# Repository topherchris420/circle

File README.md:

# CIRCLE

<div align="center">

### Close the loop. Keep the evidence.

**An open research test bench for physiological sensing, adaptive feedback, and human authority.**

[Run a session](#quick-start) · [Follow the evidence](#how-circle-works) · [Test the limits](#test-the-failure-modes) · [Human authority](#human-authority-in-the-loop) · [Explore the project](#what-you-can-examine) · [Contribute](#contributing)

<br />

<sub>One simulated session. Several physiological pathways. Every decision on the same timeline.<br />Ground truth is available to the evaluator; the controller works from device records alone.</sub>

</div>

---

**When a system senses a change and responds, what would let another researcher trust the record?**

CIRCLE makes that question runnable. It reconstructs physiological signals from simulated sensor codes, decides when haptic guidance is warranted, and preserves the evidence from the original samples through the observed cue. An independent auditor then rebuilds the session from its raw bundle.

The research ambition is a closed-loop human-state platform whose actions remain inspectable, reproducible, and subject to meaningful consent. Today, you can run the digital test bench, challenge its controller, audit its decisions, and examine a standalone cryptographic consent gate. The hardware is a design awaiting physical validation.

> [!WARNING]
> **ENGINEERING REVIEW ONLY.** Experimental research hardware and software. This repository is not approved for fabrication or human connection and does not establish medical-device, electrical-safety, EMC, or measurement-performance claims. All physiological results shown here come from simulation.

## Quick start

### Open the local workbench

The easiest way to explore CIRCLE is its local browser workbench. Choose one of
eight guided scenarios, run an active or sham session, and see the measurement
checks alongside an independent audit. Your session history, interactive reports,
and downloadable evidence stay on your computer.

```bash
git clone https://github.com/topherchris420/circle.git
cd circle
python -m pip install -r requirements.txt
python tools/run_workbench.py
```

Requires **Python 3.11+**. The browser opens at **http://127.0.0.1:8765**. Keep the
terminal running; you can close and reopen the browser tab without losing the
session. Start with **A clear signal**, then try **A loose sensor** to explore why
measurement quality and evidence integrity are separate results. No account,
device, or API key is needed. All feedback is simulated.

[Workbench guide, downloads, and troubleshooting](docs/workbench.md) ·
Use `--port 8766` if the default port is busy, or `--no-browser` to open it manually.

### Run your first session

Prefer the command line? You need **Python 3.11+**, Git, and the dependencies in [`requirements.txt`](requirements.txt). No device, account, API key, or model server is required for the simulation.

```bash
git clone https://github.com/topherchris420/circle.git
cd circle
python -m pip install -r requirements.txt
python tools/run_physiology_twin.py --output outputs/physiology --audit
```

<details>
<summary>Prefer an isolated Python environment?</summary>

After cloning and entering `circle`, create a virtual environment with `python -m venv .venv`. Activate it with `source .venv/bin/activate` on macOS/Linux or `.\.venv\Scripts\Activate.ps1` in Windows PowerShell, then run the install and experiment commands above. If your system names Python `python3`, use that command instead.

</details>

The default run simulates **six minutes**: rest, breath hold, a stressor, and recovery with adaptive haptic guidance. It also runs a matched sham arm for comparison, exports the session, scores estimates against hidden truth, and audits the exported evidence.

### Open the report and follow one decision

Open **`outputs/physiology/report.html`** in your browser. The report is self-contained: zoom the traces, open a row in the decision ledger, and follow its evidence down to the source samples.

| Question | Where to look |
| --- | --- |
| What did the controller know at that moment? | Input cutoff, availability times, features, and exact sample ranges |
| Why did it act—or hold? | Controller state, formula components, and quality-gate outcomes |
| Did the cue occur? | Command, electrical onset, and IMU-observed vibration |
| What changes when cues are withheld? | Matched sham traces, under the twin's assumed response model |
| Can the record be reconstructed? | Decision replay and independent audit verdict |

A successful reconstruction reports **`REPLAY_MATCH`**. That establishes agreement between the export and reconstruction from its inputs. The simulation scorecard separately measures agreement with the twin's truth.

To explore before running anything, open the [committed example report](diagrams/circle-physiology-session.html) locally after cloning. The image above is a static preview of that interface.

### Know what the run preserves

| Export | Purpose |
| --- | --- |
| `raw/*.csv.gz` | Sensor codes and timing records used for reconstruction |
| `session.ndjson` | Versioned device and derived records, lineage, gaps, and intervention chains |
| `closed_loop_ledger.json` | Every controller evaluation and the evidence it read |
| `analysis.json` · `scorecard.json` | Recovered estimates and checks against simulated truth |
| `truth.json` · `counterfactual.json` | Evaluator truth and the matched opposite arm; never controller inputs |
| `manifest.json` · `passport.txt` | Configuration, software provenance, artifact hashes, and session summary |
| `report.html` | Interactive view of the traces, decisions, scorecard, and execution evidence |

The [pipeline methods](docs/physiology-pipeline.md) explain how each channel and metric is derived.

## How CIRCLE works

The central question is **what gives this system grounds to act?**

A rise in heart rate is one observation. A rise in skin conductance is another. CIRCLE requires agreement across the cardiovascular and electrodermal pathways, sufficient signal quality, and a sustained observed state before guidance can begin.

| Stage | Evidence CIRCLE preserves |
| --- | --- |
| **Observe** | Raw skin conductance (EDA), optical pulse (PPG), motion (IMU), and synchronization records; device times, sequence numbers, availability, and declared gaps |
| **Infer** | Recovered physiological features, with lineage to the exact samples used |
| **Decide** | State, input cutoff, formula components, and explicit outcomes for acting, holding, or stopping |
| **Intervene** | The scheduled command, electrical onset, and vibration detected from IMU samples |
| **Reconstruct** | Analysis and derived records rebuilt from raw inputs, followed by an explicit replay verdict |

Three rules make the loop inspectable:

- **A decision can use only evidence available at the time.** A sample must have been available by the decision time and been taken at or before the input cutoff. FIFO stalls, delayed delivery, and missing samples remain visible in the record.
- **Holding is a decision.** Motion, poor contact, stale data, or disagreeing pathways can prevent guidance. After impairment, the controller requires a full clean **40-second evidence window** before treating an elevated state as sustained; repeated quality loss during guidance stops it.
- **Each stage earns its own evidence.** A command does not prove vibration, and vibration does not establish a physiological effect. `PHYSICALLY_OBSERVED` requires an observation record; in this test bench, that observation is simulated too.

The pipeline and controller consume the shared [`RawSession` boundary](models/physiology/loop.py) without importing hidden truth. The auditor reconstructs derived records instead of accepting their stored values. A derived record that disagrees with reconstruction remains detectable even if its checksums are rewritten; hashes alone do not authenticate the underlying data.

Replay names its result: `REPLAY_MATCH`, `REPLAY_DIVERGENCE`, `TIMING_VIOLATION`, `VERSION_MISMATCH`, `EVIDENCE_INTEGRITY_FAILURE`, `MISSING_SOURCE`, or `INSUFFICIENT_EVIDENCE`.

Read the [evidence contract and failure history](docs/closed-loop-evidence.md), [record schema](contracts/session-record.schema.json), and [auditor](models/physiology/audit.py).

## Test the failure modes

Change the conditions, then inspect whether the controller's behavior is justified:

```bash
# Same seed, sham arm: decisions recorded, cues withheld
python tools/run_physiology_twin.py --sham --no-counterfactual --output outputs/sham --audit

# Eight scenario families, including motion, contact loss, and timing faults
python tools/run_physiology_twin.py --scenarios --output outputs/scenarios

# Audit an existing export without rerunning the twin
python tools/audit_physiology_run.py outputs/physiology
```

The scenario suite tests both sides of the decision: refusing unwarranted guidance **and** acting when a warranted state becomes observable. A controller that always holds cannot pass. The [scenario definitions](models/physiology/scenarios.py) specify each disturbance and judge the result against hidden truth.

To inspect a deliberate loss of measurement quality, export the poor-contact scenario:

```bash
python tools/run_physiology_twin.py --scenario poor_contact --output outputs/poor-contact --audit
```

With the default seed 7, this run withholds guidance, passes **14 of 19 scorecard checks**, and returns exit code **1** because five checks fail. Its audit still reports **`REPLAY_MATCH`**: the impaired session can be reconstructed faithfully. Measurement quality and evidence integrity answer different questions. Open `outputs/poor-contact/report.html` to examine both.

The twin assumes that paced breathing changes its simulated physiology. Active-versus-sham comparisons test the software under that assumption; a physiological effect in people would need separate evidence.

## Results you can inspect

The checked-in physiology benchmark covers **50 seeds, 100–149**. Its numbers describe agreement with **simulated truth**, under the stated scoring conditions.

| Measurement | Recorded result | Evaluation condition |
| --- | --- | --- |
| Heartbeat detection | Mean F1 **0.9999** | Motion-free PPG; ±50 ms matching tolerance |
| Heart rate | Mean absolute error **0.39 bpm** | Recovered from raw sensor codes |
| HRV: RMSSD | Mean absolute error **1.5 ms** | 60-second windows |
| Respiratory rate | Mean absolute error **0.36 breaths/min** | Recovered respiratory modulation |
| Skin conductance response detection | Mean sensitivity **0.98**, positive predictive value **1.00** | Motion-free responses ≥0.05 µS |
| PPG FIFO timing | Worst error **39.18 µs** | Reconstructed sample timestamps |
| Haptic onset detection | Worst error **2.97 ms** | IMU detection versus the twin's onset |

**999 of 1,000 checks passed.** Seed 147 failed the skin-conductance response sensitivity threshold: **11 of 14 responses detected**, below the required 0.85 sensitivity. The [benchmark](docs/physiology-benchmark.json) retains the failure; the [methods](docs/physiology-pipeline.md) explain the overlapping responses and resolution limits.

**Controller 1.2.0 passed 240 of 240 runs** across eight scenario families on fresh confirmatory seeds **600–629**. The [scenario benchmark](docs/scenario-benchmark.json) records the conditions. An earlier controller passed 199 of 210 runs; its failures exposed guidance starting from an elevated state that had already resolved during a motion-obscured interval. That finding produced the clean-window precondition and evaluation on new seeds. The [evidence history](docs/closed-loop-evidence.md) preserves both rounds.

These results establish software behavior under the twin's models. Sensor accuracy, assembled-hardware performance, and human outcomes each need their own measurements.

## Human authority in the loop

CIRCLE's consent work asks a second question: **who has authority to turn a proposal into a change?** Two mechanisms address different parts of that boundary.

### Consent-by-Design

[`circle_authority.py`](circle_authority.py) implements a standalone deterministic consent gate. A restricted proposal becomes an immutable envelope containing its mutation, proposal timestamp, state-history hash, action UUID, and an initially empty signature slot. It waits as data while the loop continues processing telemetry.

| Action state | What happens |
| --- | --- |
| `PENDING_SIGNATURE` | The proposal is registered; telemetry continues; the mutation waits. |
| `EXECUTED` | Matching consent verifies against the registered Ed25519 human public key and the mutation completes; signature and execution frame are recorded. |
| `REJECTED` | Proposal, consent, or execution checks fail; no automatic retry follows. |

```bash
python tools/run_authority_demo.py
```

The demo receives a proposal at frame 1, continues telemetry through frames 2 and 3, and executes the signed mutation at frame 4. Repeated runs produce identical replay records using fixed **test-only** credentials.

**The gate is standalone; the physiological controller and protocol runner do not yet route through it.** Its signature authenticates the UUID. Durable bindings between UUIDs and envelopes, protected replay storage, and execution-time state checks are host responsibilities. The [consent integration contract](docs/consent-by-design.md) specifies these boundaries and failure behavior.

### Authorize a bounded experiment

The [protocol runner](models/protocols.py) validates proposed experiments against deterministic rules: simulation-only targets, mandatory sham arms, preserved timing margins, held-out seed checks, and corrected statistical comparisons. A named reviewer record binds authorization to the protocol's SHA-256. This record is separate from the Ed25519 consent mechanism.

<details>
<summary>Validate, authorize, and run the example protocol</summary>

```bash
python tools/run_protocol.py validate experiments/protocols/paced-breathing-arousal.json
python tools/run_protocol.py authorize experiments/protocols/paced-breathing-arousal.json --reviewer "Your Name" --output outputs/auth.json
python tools/run_protocol.py run experiments/protocols/paced-breathing-arousal.json --authorization outputs/auth.json --output outputs/protocol-result.json
```

Run the quick start first so `outputs/` exists. Review the protocol before recording authorization in your name. See the [protocol evidence contract](docs/closed-loop-evidence.md#ai-may-propose-circle-executes-the-contract) for validation and interpretation boundaries.

</details>

AI can help formulate and examine a proposal. The deterministic checks and human authorization define what may proceed.

## What you can examine

The [capability registry](capabilities.json) records implemented code, evidence, and limits. Use it to distinguish a runnable module from a design or research hypothesis.

| Area | Available now | Current boundary |
| --- | --- | --- |
| [Local workbench](docs/workbench.md) | Guided scenarios, active/sham controls, progress, cancellation, history, report viewing, and evidence downloads | Local simulation interface; no live hardware or hosted accounts |
| [Physiology pipeline](docs/physiology-pipeline.md) | Sensor reconstruction, controller, interactive report, export, and audit | Exercised against the twin |
| [Consent gate](docs/consent-by-design.md) | Ed25519 verification, immutable action envelopes, and hash-linked replay | Standalone simulation; integration remains open |
| [Acquisition](docs/hardware-sources.md) | Ingestion, clock mapping, declared gaps, simulated link faults, and recorded replay | No live biosignal device connected here |
| [OpenBCI Cyton](docs/openbci-cyton.md) | 8/16-channel ADS1299 bridge, register read-back, and an internal-signal electronic phantom | Exercised against a simulated board |
| [Oura ring](docs/hardware-sources.md#oura-ring-over-bluetooth-le-experimental-live-bridge) | Experimental BLE acquisition bridge | Exercised against a fake ring |
| [Muse Gadget](docs/hardware-sources.md) | Capability discovery, recorded refusals, protocol validation, optional operator notifications | Supplies no physiological streams; no paired-gadget validation |
| [Rev B hardware](docs/architecture.md) | Schematics, board outlines, design manifest, and engineering review gates | Designed, not built; main and optical boards unrouted |
| [Firmware](docs/timing-and-data-model.md) | Timing behavior modeled by the twin; pin map and initialization specification | Implementation remains open |

### Exercise the acquisition boundary

```bash
python tools/run_acquisition_demo.py
python tools/openbci_cyton.py self-test
python tools/muse_gadget.py capabilities --simulate
```

These examples need no hardware. **The Cyton phantom is a practical route toward physical evidence:** its ADS1299 internal test signal can supply known input through the acquisition chain without a person. The [Cyton guide](docs/openbci-cyton.md) explains the simulated scorecard and optional real-board procedure.

Every source faces the same stream contract. The Cyton provides biopotentials rather than the EDA, PPG, and other streams the physiology controller requires, so the closed loop refuses it and records why. Accepted closed-loop actuator targets are currently **`SIMULATED`** and **`NONE`**.

### From simulation to an instrument

Rev B is designed to make acquisition timing and intervention evidence observable. The **85 × 55 mm main board** combines an ESP32-S3, ADS1220 EDA front end, ICM-42688-P IMU, SDMMC storage, and DRV2605L haptics with current-edge detection. A **25 × 18 mm optical board** carries a MAX30102 red/IR sensor. Isolation, interlocks, and current limiting are design provisions awaiting independent review and measurement.

<div align="center">

<sub>Intended geometry only. Designed, not built.</sub>

</div>

[Main schematic](hardware/reports/pdf/circle-main.pdf) · [Optical schematic](hardware/reports/pdf/circle-ppg.pdf) · [Safety analysis](docs/safety-analysis.md) · [Bring-up plan](docs/board-bringup-and-validation-plan.md) · [3D viewer](diagrams/circle-3d-viewer.html)

The [checked-in verification summary](hardware/reports/verification-summary.json) records passing software scopes and **incomplete full verification** because fresh hardware checks were not run. Archived KiCad 10.0.5 schematic reports pass; PCB reports retain an open allowlist of **52 unrouted nets**. The [18 open review gates](hardware/review-gates.json) do not authorize fabrication or human use.

The next physical milestones are known-input phantoms, bench fixtures, isolation testing, and actuator loopback. The [physical evidence ladder](docs/physical-evidence-ladder.md) defines what each stage must establish before later work can proceed.

### Research extensions

The core instrument can stand independently of the research questions attached to it. The [module registry check](tools/check_module_registry.py) enforces that boundary.

| Extension | Research question or method | Evidence boundary |
| --- | --- | --- |
| [Resonance](docs/resonance-architecture.md) | Coupled-cavity models, blinded comparisons, and [falsifiable geometry hypotheses](docs/resonance-hypotheses.md) | Experimental simulation; no chamber or measured geometry effect |
| [Emergence](docs/emergence-architecture.md) | ATOM correlation search against circular-shift surrogate nulls, with family-wise correction | Exploratory associations; no causal or consciousness claim |
| [PNT](docs/quantum-pnt-architecture.md) | Translation-only 15-state estimator versus an unaided baseline on shared simulated IMU data | Simulation benchmark; quantum sensing remains speculative |
| [R.A.I.N. protocol](docs/rain-circle-experiment-protocol.md) | Versioned experiment manifest, result, and analysis contracts | Contracts here; executor elsewhere |
| [Mathematics intake](docs/MATH_RESEARCH.md) | Proposed packet-loss and clock-drift comparison with a negative control | Research design; implementation and testing remain open |

Each hypothesis needs a predefined comparison, appropriate controls, and a result that could count against it.

## Verify your scope

```bash
# Software, simulation, and deterministic artifact checks
python tools/verify_release.py --software-only

# Full package verification, requiring the pinned KiCad 10.0.5 toolchain
python tools/verify_release.py

# Inspect current review gates and derived authorization boundaries
python tools/check_review_gates.py
```

For the unit and property suite alone, run `python -m unittest discover -s tests`.

Software-only verification reports `SOFTWARE_VERIFIED` when its checks pass. Full verification requires fresh KiCad checks and reports `INCOMPLETE` if the pinned toolchain is unavailable. Neither result closes physical validation or human-use gates. See [verification scopes](docs/verification-scopes.md) and [`toolchain.json`](toolchain.json).

## Documentation

| If you want to… | Start here |
| --- | --- |
| Understand the measurement methods | [Physiology pipeline](docs/physiology-pipeline.md) |
| Examine timing, replay, and controller failures | [Closed-loop evidence](docs/closed-loop-evidence.md) |
| Integrate the consent reducer | [Consent-by-Design](docs/consent-by-design.md) |
| Add or evaluate an acquisition source | [Hardware sources](docs/hardware-sources.md) · [OpenBCI Cyton](docs/openbci-cyton.md) |
| Review the hardware design | [Architecture](docs/architecture.md) · [Safety analysis](docs/safety-analysis.md) |
| Plan physical validation | [Physical evidence ladder](docs/physical-evidence-ladder.md) · [Bring-up plan](docs/board-bringup-and-validation-plan.md) |
| Interpret verification status | [Verification scopes](docs/verification-scopes.md) · [Capability registry](capabilities.json) |

<details>
<summary>Repository map</summary>

| Path | Purpose |
| --- | --- |
| [`models/physiology/`](models/physiology) | Twin, sensors, pipeline, controller, report, evidence export, and audit |
| [`circle_authority.py`](circle_authority.py) | Consent state machine and replay payloads |
| [`models/acquisition/`](models/acquisition) | Ingestion, clock mapping, link faults, and recorded replay |
| [`models/openbci_cyton/`](models/openbci_cyton) | Cyton bridge, phantom analysis, and simulated board |
| [`models/protocols.py`](models/protocols.py) | Protocol validation, reviewer authorization, and simulation execution |
| [`models/session_records.py`](models/session_records.py) · [`contracts/`](contracts) | Record validation, provenance, lineage, and schemas |
| [`tools/`](tools) · [`tests/`](tests) | Experiments, auditors, verification tools, and regression checks |
| [`experiments/`](experiments) | Protocols and research configurations |
| [`hardware/`](hardware) | KiCad sources, interfaces, manifest, review gates, and reports |
| [`docs/`](docs) · [`diagrams/`](diagrams) | Methods, evidence boundaries, architecture, and visual explanations |

</details>

## Contributing

Useful contributions make a concrete question answerable:

- **Improve an estimator.** Compare it on fresh seeds and retain the cases where it fails.
- **Connect consent to an application path.** Define the restricted mutations, preserve durable UUID bindings, and demonstrate replay and crash-recovery behavior.
- **Strengthen acquisition.** Meet the stream and timing contracts, then exercise loss, delay, refusals, and replay. A Cyton owner can contribute an internal-signal phantom session without collecting personal biosignals.
- **Advance hardware or firmware.** Work through the review gates, timestamping requirements, and known-input validation plans.
- **Challenge a research hypothesis.** Define the comparison and a failure condition before running it; preserve the null result.

[Open an issue](https://github.com/topherchris420/circle/issues) with the question, proposed change, evidence it would produce, and a condition that would count as failure. Include the seed and replay verdict when reporting a simulation issue. [GitHub Actions](https://github.com/topherchris420/circle/actions) records current CI results.

## FAQ

<details>
<summary><strong>Can CIRCLE tell what someone is feeling?</strong></summary>

An arousal index is an engineering trigger. Physiological signals alone cannot establish a person's emotion, intent, diagnosis, or consciousness. The current twin is phenomenological and is not fitted to any person.

</details>

<details>
<summary><strong>Does consent gate every physiological cue?</strong></summary>

The Ed25519 authority module is implemented and tested independently. Wiring it into the physiological controller and protocol runner remains an open integration task.

</details>

<details>
<summary><strong>What does a passing audit establish?</strong></summary>

It establishes that the exported session satisfies the checked contracts and agrees with independent reconstruction from its raw inputs. It does not establish that those inputs accurately describe the physical world or that an intervention caused a change.

</details>

<details>
<summary><strong>Can I fabricate Rev B or connect it to a person?</strong></summary>

The boards are designed but unrouted. Fabrication and human connection remain unauthorized under the [open engineering review gates](hardware/review-gates.json). No physical sensor, bench, electrical-safety, EMC, or human-outcome validation has been performed here.

</details>

## License

[MIT](LICENSE). The license grants no approval to fabricate the hardware or connect it to a person; the engineering review boundaries above still apply.

## The premise

A human state is rarely one signal. The body offers many imperfect observations; understanding begins in the relationships among them.

CIRCLE's ambition is an instrument that can explain what it observed, account for what it changed, and preserve the person's authority over what happens next. Every experiment brings that ambition back to a record someone else can examine.

<div align="center">

**A Vers3Dynamics research project by Christopher Woodyard.**<br />
Built by one researcher. Held in common. Free to explore.

</div>

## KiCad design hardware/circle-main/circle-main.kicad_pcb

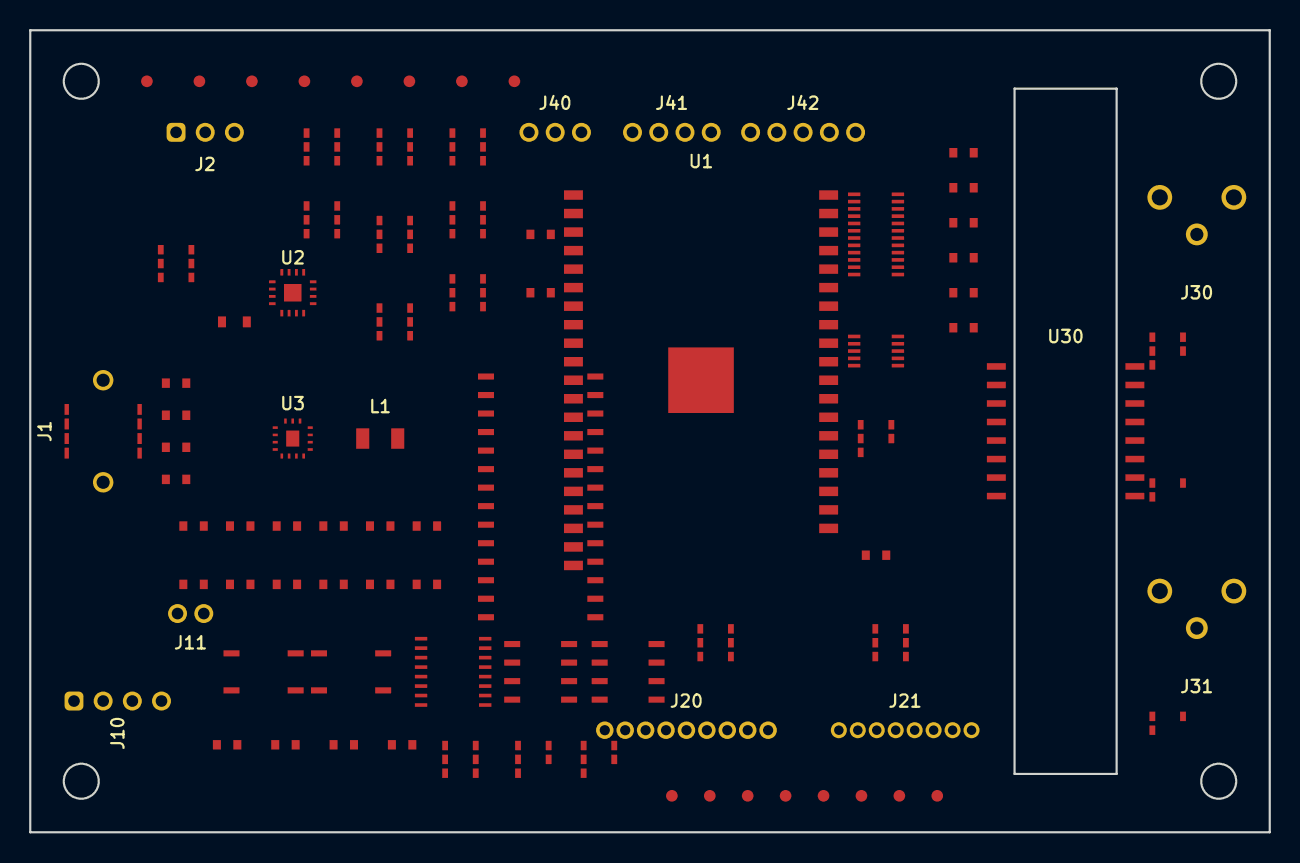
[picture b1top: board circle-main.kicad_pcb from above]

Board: 4 copper layers, 85.0 x 55.0 mm, 88 parts (0 on the bottom side), 42 nets, no tracks yet.

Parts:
D1: TPD4E05U06; SOT-23-6
D20, D21: ESD; SOT-23-6
D30: ESD_ISO; SOT-23-3
F1: USB_INPUT_FUSE; Fuse_0805
J1: USB4125-GF-A; USB_C_Receptacle
J2: LIPO_1S_NTC; JST_PH_S3B-PH-K
J10: EDA_ELECTRODES; JST_PH_S4B-PH-K
J11: CAL_INJ; Header_2P
J20: PPG_HEAD; JST_GH_9P
J21: MICROSD; Header_8P
J30: SYNC_IN_BNC; BNC_Horizontal
J31: SYNC_OUT_BNC; BNC_Horizontal
J40: HAPTIC; Header_3P
J41: INT_EXP; Header_4P
J42: EXT_EXP; Header_5P
JP1, JP2, JP3, JP4, JP5, JP6: JUMPER; R_0603
K1, K2: AQY212GS; SOIC-4
L1: 1.5uH; L_Bourns_SRN4018
Q1: SD_SW; SOT-23-6
Q2: PPG_LED_SW; SOT-23-6
Q3: HAPTIC_SW; SOT-23-6
Q4: ISO_SW; SOT-23-6
Q5: EXP_SW; SOT-23-6
Q7: EDA_SW; SOT-23-6
Q30: BSS138; SOT-23-3
R1, R2, R3, R4: 22R; R_0603
RSD1, RSD2, RSD3, RSD4, RSD5, RSD6: 33R; R_0603
RSH1, RSH2, RSH3, RSH4, RSH5, RSH6: 0.1R; R_0603
R_EDA_A1, R_EDA_A2: 49.9k; R_0603
R_EDA_B1, R_EDA_B2: 49.9k; R_0603
S1: BOOT; R_0603
S2: RESET; R_0603
S20: SAFE_EJECT; R_0603
TP1, TP2, TP3, TP4, TP5, TP6, TP7, TP8, TP9, TP10, TP11, TP12, TP13, TP14, TP15, TP16: TESTPOINT; TestPoint_Pad
U1: ESP32-S3-WROOM-1-N16R8; ESP32-S3-WROOM-1
U2: BQ24074RGTR; QFN-16-1EP
U3: TPS63070RNMR; WQFN-15-1EP
U4, U5, U13: TPS3700; SOT-23-6
U6: MCP23017; SOIC-28
U10: ADS1220; SOIC-16
U11: OPA2192; SOIC-8
U12: REF5020; SOIC-8
U14, U15: SN74LVC1G08; SOT-23-5
U20: ICM-42688-P; SOIC-24
U30: ISOW7742DWER; SOIC-16W
U31: TTL_COMP; SOT-23-5
U40: DRV2605L; SOIC-10
U41: TLV3201; SOT-23-5

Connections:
+3V3_DIG: J21.8, J41.4, JP1.2, JP2.2, JP3.2, JP4.2, JP5.2, JP6.2, L1.2, Q1.5, Q2.5, Q3.5, Q4.5, Q5.5, RSH1.2, RSH2.2, RSH3.2, RSH4.2, RSH5.2, RSH6.2, S1.2, S2.2, S20.2, TP2.1, TP4.1, TP6.1, TP8.1, TP10.1, TP12.1, TP14.1, TP16.1, U1.2, U3.5, U3.6, U3.7, U3.8, U3.9, U4.6, U5.6, U13.6, U14.5, U15.5, U30.1, U30.7, U41.3, U41.5
+3V3_EDA_A: Q7.5, U10.1, U10.16, U11.8, U12.1, U12.2, U12.7, U13.1
BAT_HUMAN_GND: D1.2, D1.5, D20.1, D20.2, D20.3, D20.4, D20.5, D20.6, D21.1, D21.2, D21.3, D21.4, D21.5, D21.6, J1.A1, J1.B1, J1.SH1, J1.SH2, J2.2, J2.3, J20.8, J20.9, J21.7, J40.3, J41.3, J42.5, K1.2, K2.2, Q1.2, Q1.4, Q1.6, Q2.2, Q2.4, Q2.6, Q3.2, Q3.4, Q3.6, Q4.2, Q4.4, Q4.6, Q5.2, Q5.4, Q5.6, Q7.2, Q7.4, Q7.6, S1.1, S2.1, S20.1, TP1.1, TP3.1, TP5.1, TP7.1, TP9.1, TP11.1, TP13.1, TP15.1, U1.1, U1.3, U1.22, U1.25, U1.26, U1.27, U1.39, U1.40, U1.41, U2.2, U2.3, U2.4, U2.5, U2.9, U2.10, U2.11, U2.12, U2.14, U2.15, U2.16, U2.17, U3.3, U3.4, U3.10, U3.13, U3.15, U3.16, U4.2, U4.4, U4.5, U5.2, U5.4, U5.5, U6.1, U6.2, U6.3, U6.4, U6.5, U6.6, U6.7, U6.8, U6.9, U6.10, U6.11, U6.12, U6.13, U6.14, U6.15, U6.16, U6.17, U6.18, U6.19, U6.20, U6.21, U6.22, U6.23, U6.24, U6.25, U6.26, U6.27, U6.28, U10.7, U10.8, U10.11, U10.12, U10.13, U10.14, U10.15, U11.4, U12.3, U12.4, U12.5, U12.6, U12.8, U13.2, U13.4, U13.5, U14.3, U15.3, U20.1, U20.2, U20.3, U20.4, U20.5, U20.6, U20.7, U20.8, U20.9, U20.10, U20.11, U20.12, U20.13, U20.14, U20.15, U20.16, U20.17, U20.18, U20.19, U20.20, U20.21, U20.22, U20.23, U20.24, U30.2, U30.6, U30.8, U40.1, U40.2, U40.3, U40.4, U40.5, U40.6, U40.7, U40.8, U40.9, U40.10, U41.2
EDA_ACTIVE: K1.1, K2.1, U15.4
EDA_ANALOG_GOOD: U13.3, U14.2
EDA_CS_N: U1.32, U10.3
EDA_DRDY: U1.37, U10.2
EDA_DRIVE_N: J10.2, J11.2, K2.3, K2.4, R_EDA_B1.1, R_EDA_B1.2, R_EDA_B2.1, R_EDA_B2.2, U11.5
EDA_DRIVE_P: J10.1, J11.1, K1.3, K1.4, R_EDA_A1.1, R_EDA_A1.2, R_EDA_A2.1, R_EDA_A2.2, U11.3
EDA_FW_REQUEST: U1.35, U14.1
EDA_MISO: U1.31, U10.6
EDA_MOSI: U1.30, U10.5
EDA_PREPARE: U14.4, U15.1
EDA_SCLK: U1.29, U10.4
EDA_SENSE_N: J10.4, U10.10, U11.6, U11.7
EDA_SENSE_P: J10.3, U10.9, U11.1, U11.2
HAPTIC_CURRENT_EDGE: J40.2, U1.36, U41.4
HAPTIC_VDRV: J40.1, U41.1
ISO_HEALTH_CHALLENGE: U1.28, U30.13
LAB_ISO_GND: D30.2, D30.3, J30.2, J30.3, J31.2, J31.3, Q30.2, U30.9, U30.14, U30.15, U31.2
PPG_INT: J20.5, U1.21
PPG_SCL_3V3: J20.4, U1.18
PPG_SDA_3V3: J20.3, U1.17
SAFETY_POWER_GOOD: Q1.1, Q2.1, Q3.1, Q4.1, Q5.1, Q7.1, U3.11, U5.3, U15.2
SD_CLK: J21.5, RSD1.1, RSD2.1, RSD3.1, RSD4.1, RSD5.1, RSD6.1, U1.4
SD_CMD: J21.6, RSD1.2, RSD2.2, RSD3.2, RSD4.2, RSD5.2, RSD6.2, U1.5
SD_D0: J21.1, U1.6
SD_D1: J21.2, U1.7
SD_D2: J21.3, U1.15
SD_D3: J21.4, U1.16
SYNC_IN_CAPTURE: U1.24, U30.3
SYNC_IN_LAB: J30.1, U30.12, U31.1, U31.4
SYNC_OUT_DRIVE: U1.23, U30.4
SYNC_OUT_LAB: D30.1, J31.1, Q30.1, Q30.3, U30.11
SYS_I2C_SCL: J41.2, U1.9
SYS_I2C_SDA: J41.1, U1.8
USB_D_MINUS: D1.3, J1.A7, J1.B7, R1.2, R2.2, R3.2, R4.2, U1.19
USB_D_PLUS: D1.1, J1.A6, J1.B6, R1.1, R2.1, R3.1, R4.1, U1.20
VBAT: J2.1, U2.13, U4.1
VBUS_5V: D1.4, D1.6, F1.1, F1.2, J1.A4, J1.B4, U2.1
VISO: U30.10, U30.16, U31.3, U31.5
V_SYS: JP1.1, JP2.1, JP3.1, JP4.1, JP5.1, JP6.1, L1.1, Q1.3, Q2.3, Q3.3, Q4.3, Q5.3, Q7.3, RSH1.1, RSH2.1, RSH3.1, RSH4.1, RSH5.1, RSH6.1, U2.6, U2.7, U3.1, U3.2, U3.12, U3.14, U5.1

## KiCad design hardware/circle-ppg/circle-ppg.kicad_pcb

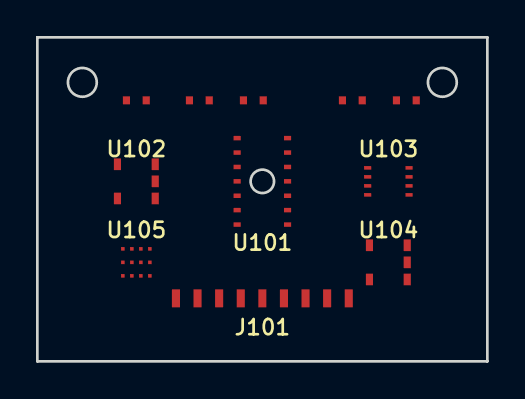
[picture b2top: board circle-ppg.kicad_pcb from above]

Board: 4 copper layers, 25.0 x 18.0 mm, 11 parts (0 on the bottom side), 10 nets, no tracks yet.

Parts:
C101: 1.0uF; R_0402
C102: 10uF; R_0402
D101: ESD; R_0402
J101: PPG_HEAD; JST_GH_9P
R101, R102: 33R; R_0402
U101: MAX30102; OLGA-14
U102: LP5907MFX-1.8; SOT-23-5
U103: TXS0102DCUR; VSSOP-8
U104: AT24CS02; SOT-23-5
U105: LIS2DW12; LGA-12

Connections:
PPG_1V8: C101.1, U101.2, U101.3, U102.5, U103.1
PPG_3V3: D101.1, J101.1, U102.1, U102.3, U103.5, U103.8, U104.5
PPG_INT: J101.5, U101.6
PPG_LED_GND: C102.2, J101.9, U101.11, U101.12, U101.13
PPG_LED_PWR: C102.1, J101.2, U101.10
PPG_LOGIC_GND: C101.2, D101.2, J101.8, U101.1, U101.7, U101.8, U101.9, U101.14, U102.2, U102.4, U103.4, U104.2, U104.4, U105.1, U105.2, U105.3, U105.4, U105.5, U105.6, U105.7, U105.8, U105.9, U105.10, U105.11, U105.12
PPG_SCL_1V8: U101.5, U103.3
PPG_SCL_3V3: J101.4, R102.1, R102.2, U103.6, U104.1
PPG_SDA_1V8: U101.4, U103.2
PPG_SDA_3V3: J101.3, R101.1, R101.2, U103.7, U104.3

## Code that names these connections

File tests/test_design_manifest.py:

import io
import json
import pathlib
import unittest
from contextlib import redirect_stdout
from unittest import mock

import tools.check_design_manifest as checker

ROOT = pathlib.Path(__file__).resolve().parents[1]
EXPECTED_CIRCLE_MAIN_SHEETS = [
    "00_root",
    "01_compute_usb",
    "02_power",
    "03_eda_safety",
    "04_sensors",
    "05_storage",
    "06_sync_isolation",
    "07_feedback_expansion",
    "08_observability",
]
EXPECTED_CIRCLE_PPG_SHEETS = ["00_ppg_root"]
EXPECTED_CONNECTORS = [
    {"name": "USB_C", "domain": "BAT_HUMAN", "eda_policy": "forces_disabled", "pins": ["VBUS_5V", "USB_DN", "USB_DP", "USB_CC1", "USB_CC2", "USB_SHIELD"]},
    {"name": "BATTERY", "domain": "BAT_HUMAN", "eda_policy": "internal_only", "pins": ["BAT_POS", "BAT_NEG", "BAT_NTC"]},
    {"name": "EDA_ELECTRODES", "domain": "BAT_HUMAN", "eda_policy": "internal_only", "pins": ["EDA_DRIVE_P", "EDA_DRIVE_N", "EDA_SENSE_P", "EDA_SENSE_N"]},
    {"name": "PPG_HEAD", "domain": "BAT_HUMAN", "eda_policy": "internal_only", "pins": ["PPG_3V3", "PPG_LED_PWR", "PPG_SDA_3V3", "PPG_SCL_3V3", "PPG_INT", "PPG_MOTION_INT", "PPG_BOARD_ID", "PPG_LOGIC_GND", "PPG_LED_GND"]},
    {"name": "SYNC_IN_BNC", "domain": "LAB_ISO", "eda_policy": "isolated", "pins": ["SYNC_IN_LAB", "LAB_ISO_GND"]},
    {"name": "SYNC_OUT_BNC", "domain": "LAB_ISO", "eda_policy": "isolated", "pins": ["SYNC_OUT_LAB", "LAB_ISO_GND"]},
    {"name": "DEBUG", "domain": "BAT_HUMAN", "eda_policy": "forces_disabled", "pins": ["UART_TX", "UART_RX", "DEBUG_ATTACHED", "BAT_HUMAN_GND"]},
    {"name": "INTERNAL_EXPANSION", "domain": "BAT_HUMAN", "eda_policy": "internal_only", "pins": ["I2C_SDA_3V3", "I2C_SCL_3V3", "GPIO_EXP_INT", "BAT_HUMAN_GND"]},
    {"name": "EXTERNAL_EXPANSION", "domain": "BAT_HUMAN", "eda_policy": "forces_disabled", "pins": ["EXP_3V3", "EXP_UART_TX", "EXP_UART_RX", "EXTERNAL_EXPANSION_ATTACHED", "BAT_HUMAN_GND"]},
    {"name": "HAPTIC", "domain": "BAT_HUMAN", "eda_policy": "internal_only", "pins": ["HAPTIC_VDRV", "HAPTIC_CURRENT_EDGE", "BAT_HUMAN_GND"]},
    {"name": "MICROSD", "domain": "BAT_HUMAN", "eda_policy": "internal_only", "pins": ["SD_D0", "SD_D1", "SD_D2", "SD_D3", "SD_CLK", "SD_CMD", "BAT_HUMAN_GND"]},
]


class DesignManifestTest(unittest.TestCase):
    @classmethod
    def setUpClass(cls):
        cls.design = json.loads((ROOT / "hardware/design-manifest.json").read_text(encoding="utf-8"))
        cls.interfaces = json.loads((ROOT / "hardware/interfaces.json").read_text(encoding="utf-8"))

    def test_mainboard_sheet_set_is_exact(self):
        names = [sheet["name"] for sheet in self.design["boards"]["circle-main"]["sheets"]]
        self.assertEqual(names, EXPECTED_CIRCLE_MAIN_SHEETS)

    def test_ppg_sheet_set_is_exact(self):
        names = [sheet["name"] for sheet in self.design["boards"]["circle-ppg"]["sheets"]]
        self.assertEqual(names, EXPECTED_CIRCLE_PPG_SHEETS)

    def test_safety_terms_are_hardware_nets(self):
        nets = set(self.design["required_nets"])
        self.assertTrue({
            "EDA_PREPARE", "EDA_ACTIVE", "BATTERY_VALID", "USB_PRESENT",
            "DEBUG_ATTACHED", "EXTERNAL_EXPANSION_ATTACHED",
            "SAFETY_POWER_GOOD", "EDA_ANALOG_GOOD"
        }.issubset(nets))

    def test_reference_designators_are_unique(self):
        refs = [part["ref"] for part in self.design["parts"]]
        self.assertEqual(len(refs), len(set(refs)))

    def test_connector_contract_is_exact(self):
        self.assertEqual(self.interfaces["connectors"], EXPECTED_CONNECTORS)

    def test_lab_iso_ground_only_appears_on_lab_iso_connectors(self):
        for connector in self.interfaces["connectors"]:
            if "LAB_ISO_GND" in connector["pins"]:
                self.assertEqual(connector["domain"], "LAB_ISO")

    def test_lab_iso_connectors_never_expose_bat_human_ground(self):
        for connector in self.interfaces["connectors"]:
            if connector["domain"] == "LAB_ISO":
                self.assertNotIn("BAT_HUMAN_GND", connector["pins"])


class DesignManifestCheckerTest(unittest.TestCase):
    def test_validate_reports_missing_required_structure(self):
        errors = checker.validate({}, {})
        self.assertIn("design: missing or invalid boards", errors)
        self.assertIn("interfaces: missing or invalid connectors", errors)

    def test_validate_reports_non_dict_root_objects(self):
        errors = checker.validate([], [])
        self.assertIn("design: root must be an object", errors)
        self.assertIn("interfaces: root must be an object", errors)

    def test_main_reports_stable_error_for_unreadable_json(self):
        output = io.StringIO()
        with mock.patch("tools.check_design_manifest.json.loads", side_effect=json.JSONDecodeError("bad json", "x", 0)):
            with redirect_stdout(output):
                exit_code = checker.main()

        self.assertEqual(exit_code, 1)
        self.assertEqual(output.getvalue().splitlines(), ["ERROR: failed to read design/interface JSON"])


if __name__ == "__main__":
    unittest.main()

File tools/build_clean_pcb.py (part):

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    for i in range(21):
        pin = str(i + 1)
        py = -12.7 + i * 1.27
        net = "+3V3_DIG" if pin == "2" else "BAT_HUMAN_GND"
        if pin == "4": net = "SD_CLK"
        elif pin == "5": net = "SD_CMD"
        elif pin == "6": net = "SD_D0"
        elif pin == "7": net = "SD_D1"
        elif pin == "8": net = "SYS_I2C_SDA"
        elif pin == "9": net = "SYS_I2C_SCL"
        elif pin == "10": net = "IMU_SCLK"
        elif pin == "11": net = "IMU_MOSI"
        elif pin == "12": net = "IMU_MISO"
        elif pin == "13": net = "IMU_CS_N"
        elif pin == "14": net = "IMU_DRDY"
        elif pin == "15": net = "SD_D2"
        elif pin == "16": net = "SD_D3"
        elif pin == "17": net = "PPG_SDA_3V3"
        elif pin == "18": net = "PPG_SCL_3V3"
        elif pin == "19": net = "USB_D_MINUS"
        elif pin == "20": net = "USB_D_PLUS"
        elif pin == "21": net = "PPG_INT"
        esp_pads.append(make_pad(pin, -8.75, py, net, size="1.3 0.65"))

    for i in range(19):
        pin = str(i + 22)
        py = 12.7 - (i + 2) * 1.27
        net = "BAT_HUMAN_GND"
        if pin == "23": net = "SYNC_OUT_DRIVE"
        elif pin == "24": net = "SYNC_IN_CAPTURE"
        elif pin == "28": net = "ISO_HEALTH_CHALLENGE"
        elif pin == "29": net = "EDA_SCLK"
        elif pin == "30": net = "EDA_MOSI"
        elif pin == "31": net = "EDA_MISO"
        elif pin == "32": net = "EDA_CS_N"
        elif pin == "33": net = "UART_TX"
        elif pin == "34": net = "UART_RX"
        elif pin == "35": net = "EDA_FW_REQUEST"
        elif pin == "36": net = "HAPTIC_CURRENT_EDGE"
        elif pin == "37": net = "EDA_DRDY"
        elif pin == "38": net = "SYS_STATUS_INT_N"
        esp_pads.append(make_pad(pin, 8.75, py, net, size="1.3 0.65"))

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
